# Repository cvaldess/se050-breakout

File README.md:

# SE050 Breakout

A minimal breakout board for the **NXP EdgeLock SE050E2HQ1** secure element, bringing the I²C
interface out to a 5-pin 2 mm header. 16.42 × 14.56 mm, two layers, all passives 0402.

Designed in KiCad 10. The project is self-contained: the SE050 symbol, footprint and 3D model live
in this repository, so it opens on any machine without installing extra libraries.

## Where to buy

The whole design is here — schematic, layout, gerbers, symbol and footprint — and it is meant to be
built. If you would rather not reflow a 3 × 3 mm QFN with a ground pad under it, assembled boards
are available:

also

**[Buy an assembled breakout →](https://meshtastic.cvaldess.com/se050)** — €15. Ships from Spain to
the EU.

Nothing is held back for the sale: send [`gerber/`](gerber/) to any board house and you get the same
board. Read the fabrication status note below before ordering either way.

## Pinout (J1, 1×5, 2 mm pitch)

| Pin | Net | Notes |
|----|------|-------|
| 1 | +3.3V | supply, feeds VIN (pin 12) |
| 2 | SDA | I²C data, 4.7 kΩ pull-up on board |
| 3 | SCL | I²C clock, 4.7 kΩ pull-up on board |
| 4 | ENA | enable — **drive high to use the chip**, or close JP1 (see below) |
| 5 | GND | |

**ENA is not optional — this is the first thing to get wrong.** R3 pulls it to ground, so the SE050
powers up in deep power-down and will **not answer on I²C** until ENA goes high. If your scan of the
bus finds nothing at 0x48, this is almost certainly why.

You have two ways to handle it:

- **Drive ENA from a GPIO** (pin 4 of the header). This is the reason the pin is broken out: it
  gives the host a hard power switch over the secure element, and deep power-down draws under 5 µA.
- **Close JP1** if you have no pin to spare. It is a solder jumper on the **top side**, labelled on
  the silkscreen, and it ships **open** — bridge the two pads with solder and the chip is
  permanently enabled. Leave pin 4 of the header unconnected in that case.

Closing JP1 costs you only the deep power-down mode, which is the one mode controlled by that pad.
Software power-down (~430–480 µA, with state retention, woken by a falling edge on SDA) still works
either way. It also leaves R3 as a permanent 100 kΩ load across the rail, about 33 µA.

Note that firmware commonly ignores this pin — the Meshtastic SE050 driver, for one, never touches
it — so if you are dropping this board under existing software, JP1 is probably what you want.

The I²C target address of the SE050 is **0x48**.

## Bill of materials

| Ref | Value | Footprint | LCSC | Purpose |
|-----|-------|-----------|------|---------|
| SE050 | SE050E2HQ1/Z01Z3Z | HX2QFN20 3×3 mm | C5190917 | secure element |
| C1 | 100 nF | 0402 | C1525 | VIN decoupling |
| C2 | 33 nF | 0402 | C106862 | ENA filtering |
| R1, R2 | 4.7 kΩ | 0402 | C105871 | I²C pull-ups to 3V3 |
| R3 | 100 kΩ | 0402 | C60491 | ENA pull-down |
| J1 | 1×5 header | 2 mm pitch | — | breakout header |
| JP1 | — | solder jumper, top side | — | ties ENA to 3V3; **ships open** |
| H1 | — | M2 | — | mounting hole, tied to GND |
| FID1, FID2 | — | 1 mm fiducial | — | optical alignment for automated assembly |

Only the five parts with an LCSC number are fitted by machine; J1, JP1 and H1 are hand work or
nothing at all.

**There is deliberately no capacitor between VOUT (pin 15) and VCC (pin 18).** Application note
AN13483 §8.2.2 asks for that node to be left undecoupled on an I²C part that uses deep power-down,
and this board follows it. Two builds were made to test the point — one with a 33 nF there and one
without — and they were indistinguishable across every measurement available without an
oscilloscope: identical enable/disable timing, identical 1 µA deep power-down current, and the same
result on every functional test. The note is obeyed because obeying it costs nothing, not because a
failure was reproduced.

## Design notes

Worth reading before you reuse this in your own layout — most of it comes straight from the
[SE050 data sheet](https://www.nxp.com/products/SE050) and is easy to get wrong.

**The ISO7816 pins are left unconnected on purpose.** The SE050 also speaks ISO7816 and ISO14443
as a smart card, but that interface is *not enabled* in generic SE050 configurations — NXP enables
it only on customer request (see AN12436, which does not list it for any stock part number). On the
E2 those pads are inert, and the data sheet's own recommendation for pins 3 (IO1), 13 (CLK) and
16 (IO2) is *"n.c. (recommended)"*.

**Pin 14 (RST_N) is the exception, and it goes to ground here.** For that pad the data sheet offers
no floating option — *"if not used then connect to VCC or VSS"* — and of the two, VSS is the one
that holds up in every state of this board. RST_N is referenced to VCC, and VCC is fed from VOUT
through an internal switch that opens in deep power-down: with ENA low, VCC drops to 0 V while VIN
stays up, so a pin tied to the 3V3 rail would sit above its own reference. Ground sidesteps that,
and it cannot hold the part in reset because RST_N is only active when the ISO7816 interface is
enabled, which it is not on the E2.

Note that IO1 and IO2 double as the **I²C controller** pins (SDA and SCL respectively) — the SE050
acting as a bus master to talk directly to a sensor and sign its readings. The E2 supports that at
up to 1 Mbit/s. If you want it, those are the pads to break out.

**VOUT is a switch, not a regulator.** Pin 15 (VOUT) supplies pin 18 (VCC) through an internal
power switch of about 1.1 Ω, which is why they are tied together here — the arrangement the data
sheet requires for deep power-down to work. In deep power-down VOUT and VCC are switched off
entirely and only the I²C pads stay supplied from VIN.

**The exposed pad is ground.** It is stitched to the ground plane with five 0.6 mm vias (0.3 mm
drill) — four at the corners and one in the centre — leaving 0.175 mm of clearance at the tightest
to the edge of the 1.95 × 1.95 mm pad. If you have the stencil made, check that your fab tents the via barrels, or
solder will wick down them during reflow.

**Two fiducials, diagonally opposite, for machine assembly.** Each is a 1 mm copper dot in a 2 mm
solder mask opening, with a 3 mm keepout drawn as a rule area on the top copper so the ground pour
backs away and leaves the camera a clean target. If you hand-solder this board they are simply two
bare copper dots and you can ignore them. Note that the keepout is a top-layer rule: the bottom pour
runs straight under the fiducials, which is fine, because the camera cannot see through the board.

## Fabrication

Everything the board house needs is in [`gerber/`](gerber/), unzipped:

- Gerbers for both copper layers, both solder masks, the top silkscreen and the board outline
- **Paste layers for both sides** (`.gtp` / `.gbp`), for ordering a stencil
- Excellon drill files, plated and non-plated separately, plus drill maps

There is **no bottom silkscreen** — the layer is empty and is not exported, which keeps the board on
the cheaper single-sided legend option.

Two-layer board, 1.6 mm, no controlled impedance, nothing exotic. Copper pours are filled in the
exported gerbers.

> **Fabrication status, precisely.** An earlier revision of this layout — same schematic, same
> stack-up, 16.33 × 12.72 mm and without the fiducials — was manufactured, assembled by hand and
> validated on hardware: the SE050 answers on 0x48, a full SCP03 session opens, keys are generated
> and survive a power cycle, deep power-down measures 1 µA, and 30 consecutive enable/disable cycles
> ran without a fault. The solder jumper JP1 was exercised too.
>

## License

GPL-3.0 — see [LICENSE](LICENSE).

## Repository layout

```
se050_breakout.kicad_pro / .kicad_sch / .kicad_pcb
SE050E2HQ1.kicad_sym                 symbol
SE050E2HQ1.pretty/                   footprint + STEP model
sym-lib-table / fp-lib-table         point at the two above via ${KIPRJMOD}
gerber/                              fabrication output
```

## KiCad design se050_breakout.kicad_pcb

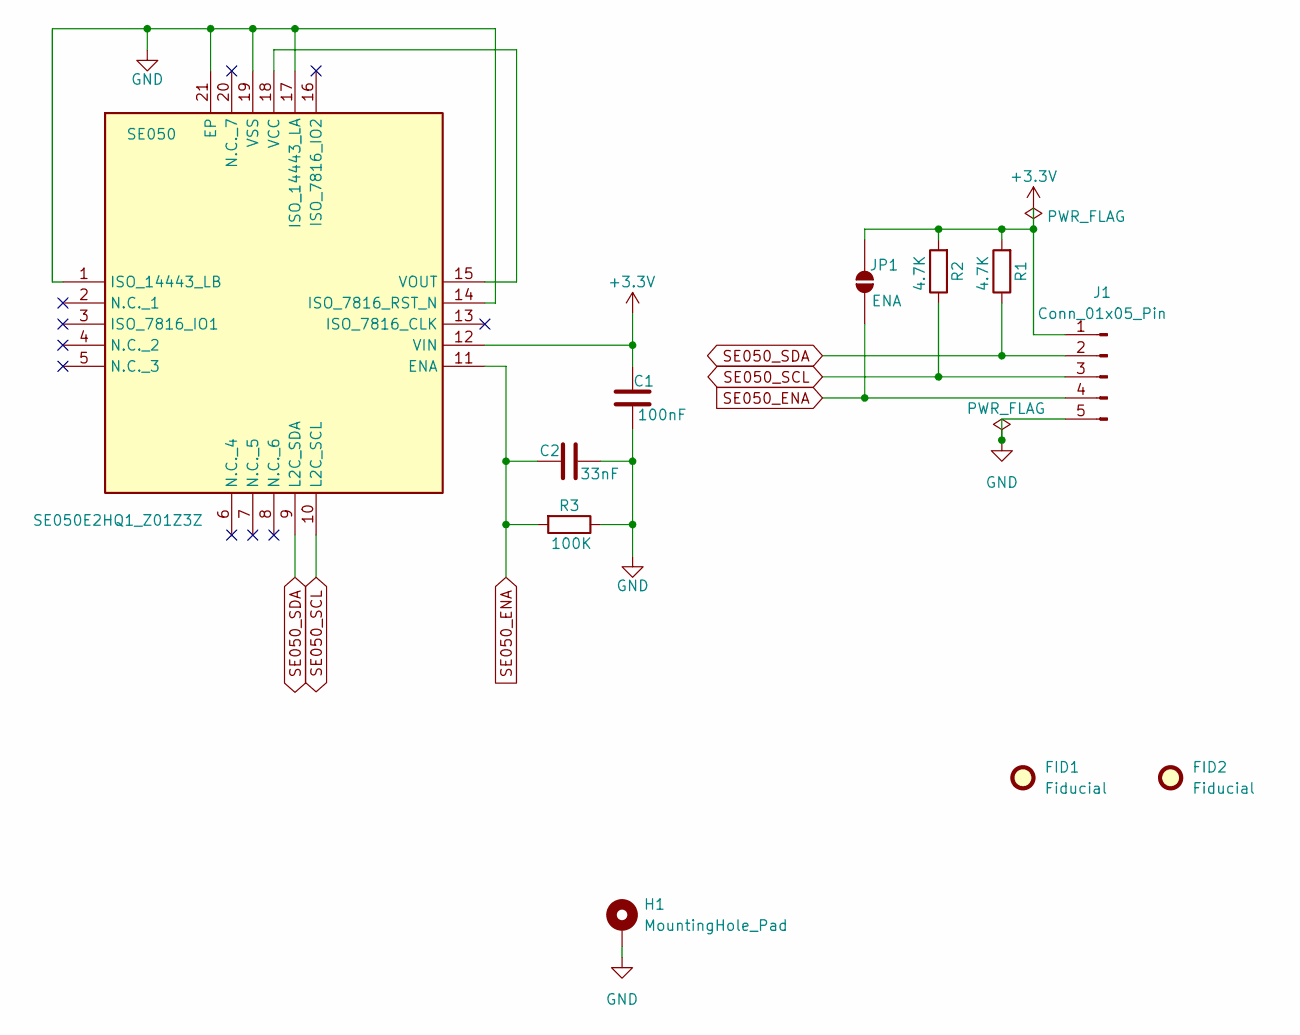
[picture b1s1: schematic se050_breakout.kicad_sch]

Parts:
C1: 100nF; C_0402_1005Metric; LCSC Part C1525
C2: 33nF; C_0402_1005Metric; LCSC Part C106862
FID1, FID2: Fiducial; Fiducial_1mm_Mask2mm
H1: MountingHole_Pad; MountingHole_2.2mm_M2_DIN965_Pad
J1: Conn_01x05_Pin; PinHeader_1x05_P2.00mm_Vertical
JP1: ENA; SolderJumper-2_P1.3mm_Open_RoundedPad1.0x1.5mm
R1, R2: 4.7K; R_0402_1005Metric; LCSC Part C105871
R3: 100K; R_0402_1005Metric; LCSC Part C60491
SE050: SE050E2HQ1_Z01Z3Z; QFN40P300X300X33-21N-D; MANUFACTURER_PART_NUMBER SE050E2HQ1/Z01Z3Z; Mouser Part Number 771-SE050E2HQ1Z01Z3Z

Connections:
+3.3V: C1.1, J1.1, JP1.2 (B), R1.2, R2.2, SE050.12 (VIN)
GND: C1.2, C2.2, H1.1 (1_1), J1.5, R3.1, SE050.1 (ISO_14443_LB), SE050.14 (ISO_7816_RST_N), SE050.17 (ISO_14443_LA), SE050.19 (VSS), SE050.21 (EP)
unnamed: SE050.15 (VOUT), SE050.18 (VCC)
SE050_ENA: C2.1, J1.4, JP1.1 (A), R3.2, SE050.11 (ENA)
SE050_SCL: J1.3, R2.1, SE050.10 (L2C_SCL)
SE050_SDA: J1.2, R1.1, SE050.9 (L2C_SDA)

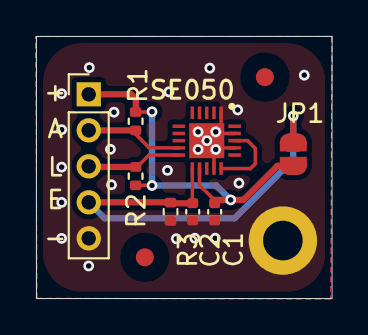
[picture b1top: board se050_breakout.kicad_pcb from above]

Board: 2 copper layers, 16.4 x 14.6 mm, 11 parts (0 on the bottom side), 6 nets.
